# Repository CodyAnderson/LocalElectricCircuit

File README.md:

# LocalElectricCircuit

This is the repository containing the Circuit board files for the Global Electric Circuit project.

Other Global Electric Circuit project repositories can be found at:

| Repository                                                                  | Description         |
|:--------------------------------------------------------------------------- |:------------------  |
| [GlobalCircuit](https://github.com/keleuk/GlobalCircuit)                    | PIC32 code          |
| [GECaux](https://github.com/keleuk/GECaux)                                  | PIC16 code          |
| [GECutils](https://github.com/keleuk/GECutils)                              | Python scripts      |
| [LocalElectricCircuit](https://github.com/CodyAnderson/LocalElectricCircuit)| Circuit board files |

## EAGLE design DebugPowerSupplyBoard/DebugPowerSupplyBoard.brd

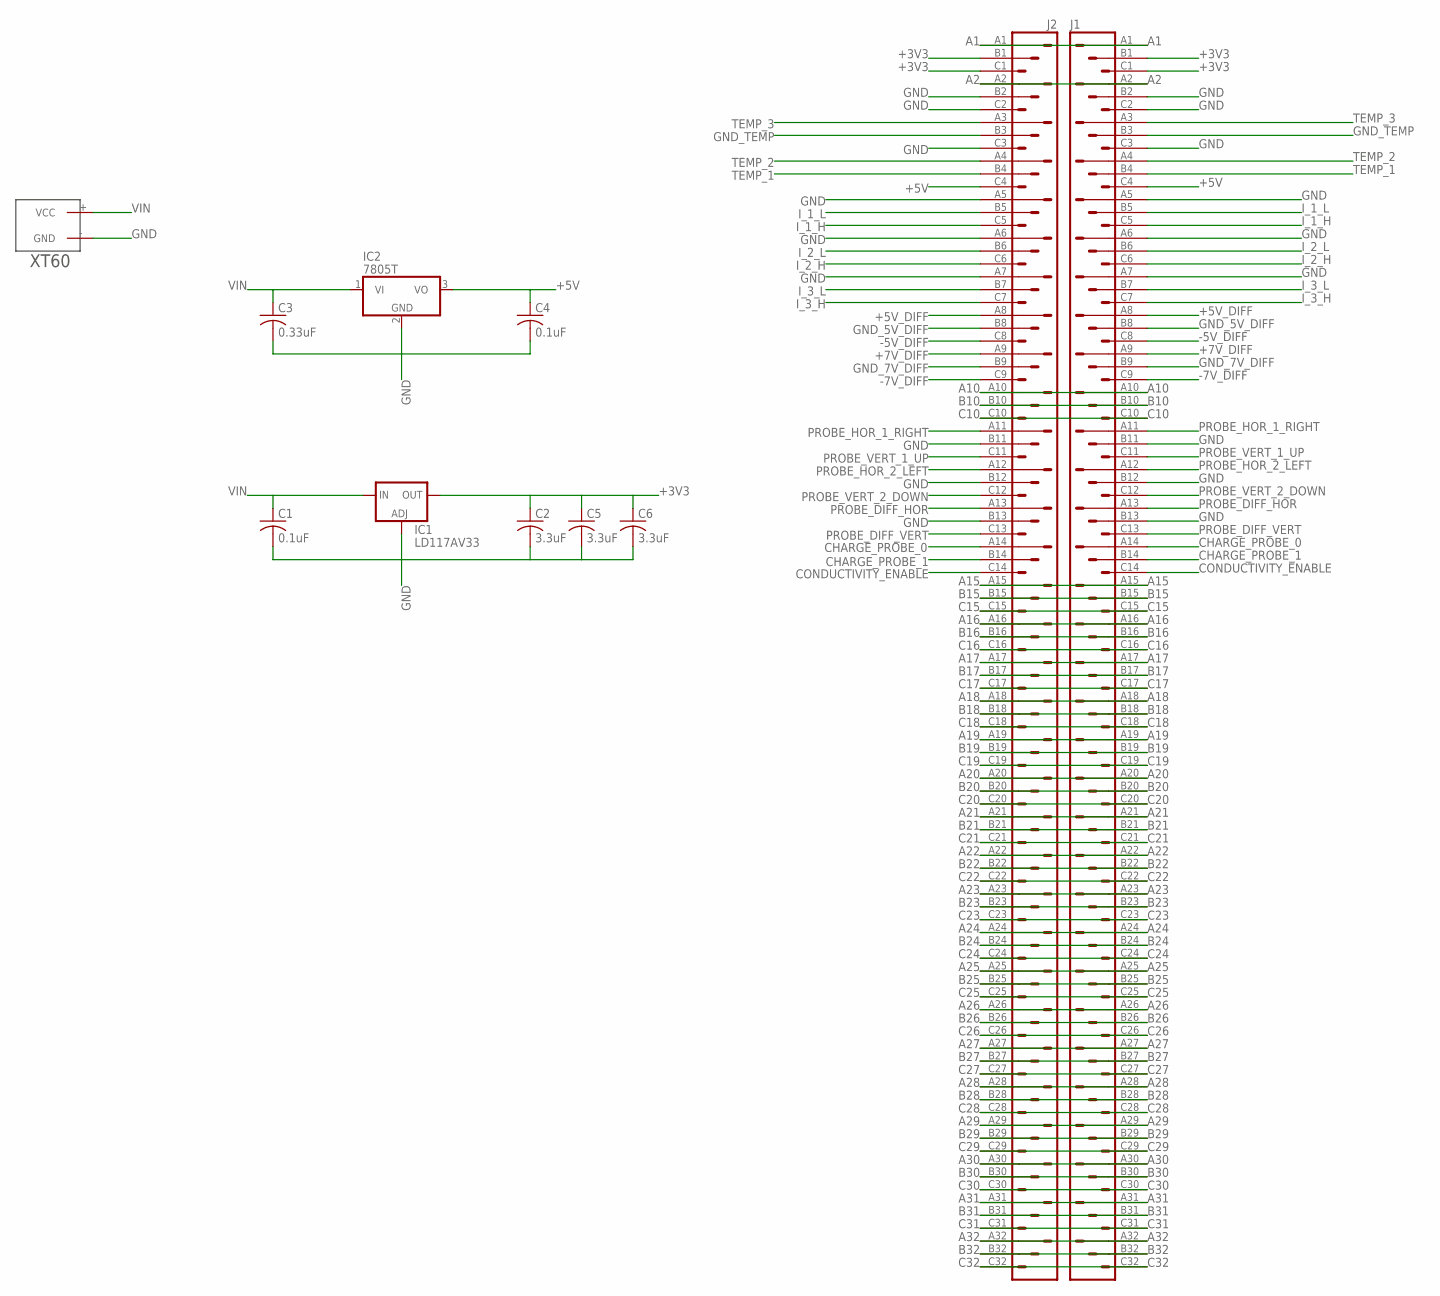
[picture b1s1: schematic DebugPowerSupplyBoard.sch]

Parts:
C1, C4: 0.1uF; C050-025X075
C2, C5, C6: 3.3uF; C050-055X075
C3: 0.33uF; C050-035X075
IC1: LD117AV33; TO220L1
IC2: 7805T; TO220H
J1, J2: VG96KB
U$6: XT60

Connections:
+3V3: C2.1, C5.1, C6.1, IC1.2 (OUT), J1.B1, J1.C1, J2.B1, J2.C1
+5V: C4.1, IC2.3 (VO), J1.C4, J2.C4
+5V_DIFF: J1.A8, J2.A8
+7V_DIFF: J1.A9, J2.A9
-5V_DIFF: J1.C8, J2.C8
-7V_DIFF: J1.C9, J2.C9
A1: J1.A1, J2.A1
A2: J1.A2, J2.A2
A10: J1.A10, J2.A10
A15: J1.A15, J2.A15
A16: J1.A16, J2.A16
A17: J1.A17, J2.A17
A18: J1.A18, J2.A18
A19: J1.A19, J2.A19
A20: J1.A20, J2.A20
A21: J1.A21, J2.A21
A22: J1.A22, J2.A22
A23: J1.A23, J2.A23
A24: J1.A24, J2.A24
A25: J1.A25, J2.A25
A26: J1.A26, J2.A26
A27: J1.A27, J2.A27
A28: J1.A28, J2.A28
A29: J1.A29, J2.A29
A30: J1.A30, J2.A30
A31: J1.A31, J2.A31
A32: J1.A32, J2.A32
B10: J1.B10, J2.B10
B15: J1.B15, J2.B15
B16: J1.B16, J2.B16
B17: J1.B17, J2.B17
B18: J1.B18, J2.B18
B19: J1.B19, J2.B19
B20: J1.B20, J2.B20
B21: J1.B21, J2.B21
B22: J1.B22, J2.B22
B23: J1.B23, J2.B23
B24: J1.B24, J2.B24
B25: J1.B25, J2.B25
B26: J1.B26, J2.B26
B27: J1.B27, J2.B27
B28: J1.B28, J2.B28
B29: J1.B29, J2.B29
B30: J1.B30, J2.B30
B31: J1.B31, J2.B31
B32: J1.B32, J2.B32
C10: J1.C10, J2.C10
C15: J1.C15, J2.C15
C16: J1.C16, J2.C16
C17: J1.C17, J2.C17
C18: J1.C18, J2.C18
C19: J1.C19, J2.C19
C20: J1.C20, J2.C20
C21: J1.C21, J2.C21
C22: J1.C22, J2.C22
C23: J1.C23, J2.C23
C24: J1.C24, J2.C24
C25: J1.C25, J2.C25
C26: J1.C26, J2.C26
C27: J1.C27, J2.C27
C28: J1.C28, J2.C28
C29: J1.C29, J2.C29
C30: J1.C30, J2.C30
C31: J1.C31, J2.C31
C32: J1.C32, J2.C32
CHARGE_PROBE_0: J1.A14, J2.A14
CHARGE_PROBE_1: J1.B14, J2.B14
CONDUCTIVITY_ENABLE: J1.C14, J2.C14
GND: C1.2, C2.2, C3.2, C4.2, C5.2, C6.2, IC1.1 (ADJ), IC2.2 (GND), J1.A5, J1.A6, J1.A7, J1.B2, J1.B11, J1.B12, J1.B13, J1.C2, J1.C3, J2.A5, J2.A6, J2.A7, J2.B2, J2.B11, J2.B12, J2.B13, J2.C2, J2.C3, U$6.- (GND)
GND_5V_DIFF: J1.B8, J2.B8
GND_7V_DIFF: J1.B9, J2.B9
GND_TEMP: J1.B3, J2.B3
I_1_H: J1.C5, J2.C5
I_1_L: J1.B5, J2.B5
I_2_H: J1.C6, J2.C6
I_2_L: J1.B6, J2.B6
I_3_H: J1.C7, J2.C7
I_3_L: J1.B7, J2.B7
PROBE_DIFF_HOR: J1.A13, J2.A13
PROBE_DIFF_VERT: J1.C13, J2.C13
PROBE_HOR_1_RIGHT: J1.A11, J2.A11
PROBE_HOR_2_LEFT: J1.A12, J2.A12
PROBE_VERT_1_UP: J1.C11, J2.C11
PROBE_VERT_2_DOWN: J1.C12, J2.C12
TEMP_1: J1.B4, J2.B4
TEMP_2: J1.A4, J2.A4
TEMP_3: J1.A3, J2.A3
VIN: C1.1, C3.1, IC1.3 (IN), IC2.1 (VI), U$6.+ (VCC)

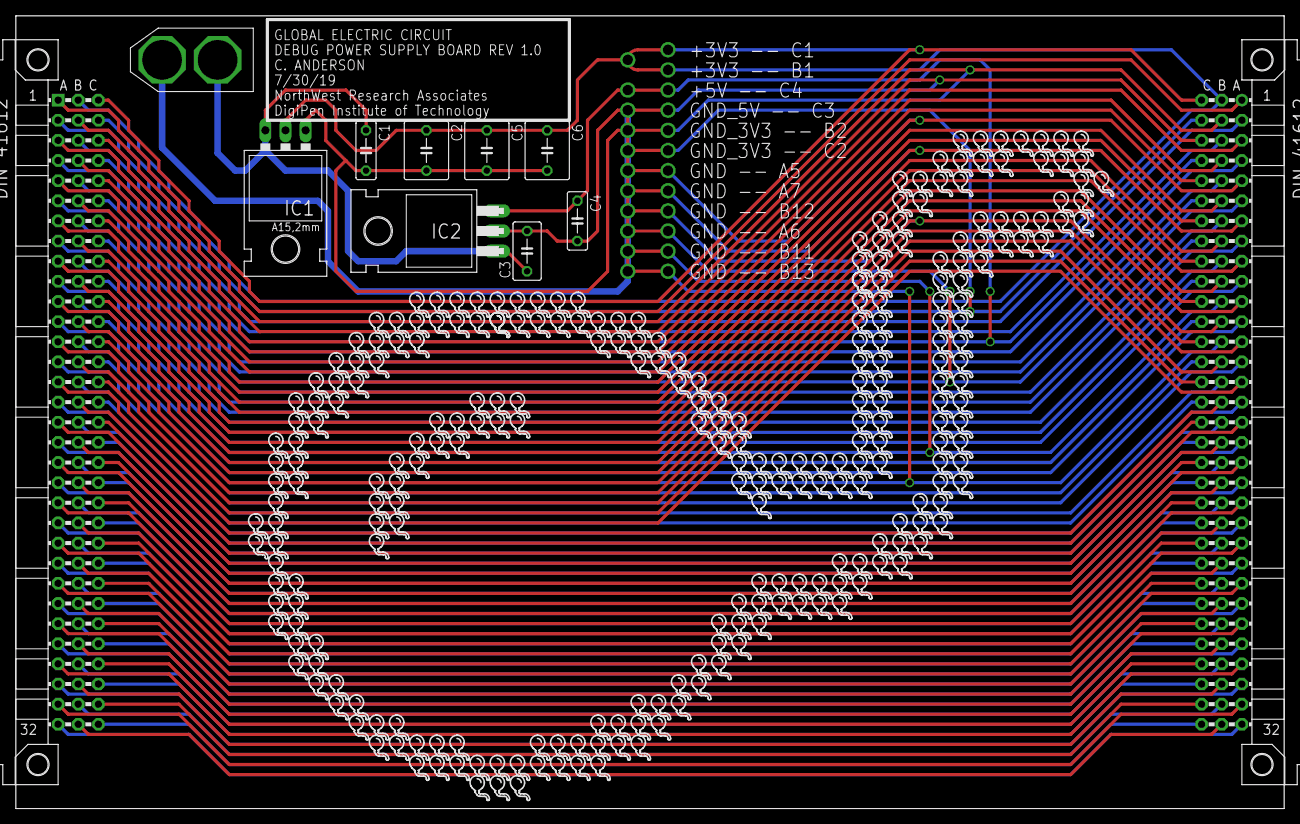
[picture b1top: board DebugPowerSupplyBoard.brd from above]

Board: 2 copper layers, 160.0 x 100.0 mm, 281 parts (0 on the bottom side), 88 nets.

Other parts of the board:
U$21, U$273, U$274, U$275, U$276, U$277, U$278, U$279, U$280, U$281, U$282, U$283, U$284, U$285, U$286, U$287, U$288, U$289, U$290, U$291, U$292, U$293, U$294, U$295, U$296, U$297, U$298, U$299, U$300, U$301, U$302, U$303, U$304, U$305, U$306, U$307, U$308, U$309, U$310, U$311, U$312, U$313, U$314, U$315, U$316, U$317, U$318, U$319, U$320, U$321, U$322, U$323, U$324, U$325, U$326, U$327, U$328, U$329, U$330, U$331, U$332, U$333, U$334, U$335, U$336, U$337, U$338, U$339, U$340, U$341, U$342, U$343, U$344, U$345, U$346, U$347, U$348, U$349, U$350, U$351, U$352, U$353, U$354, U$355, U$356, U$357, U$358, U$359, U$360, U$361, U$362, U$363, U$364, U$365, U$366, U$367, U$368, U$369, U$370, U$371, U$372, U$373, U$374, U$375, U$376, U$377, U$378, U$379, U$380, U$381, U$382, U$383, U$384, U$385, U$386, U$387, U$388, U$389, U$390, U$391, U$392, U$393, U$394, U$395, U$396, U$397, U$398, U$399, U$400, U$401, U$402, U$403, U$404, U$405, U$406, U$407, U$408, U$409, U$410, U$411, U$412, U$413, U$414, U$415, U$416, U$417, U$418, U$419, U$420, U$421, U$422, U$423, U$424, U$425, U$426, U$427, U$428, U$429, U$430, U$431, U$432, U$433, U$434, U$435, U$436, U$437, U$438, U$439, U$440, U$441, U$442, U$443, U$444, U$445, U$446, U$447, U$448, U$449, U$450, U$451, U$452, U$453, U$454, U$455, U$456, U$457, U$458, U$459, U$460, U$461, U$462, U$463, U$464, U$465, U$466, U$467, U$468, U$469, U$470, U$471, U$472, U$473, U$474, U$475, U$476, U$477, U$478, U$479, U$480, U$481, U$482, U$483, U$484, U$485, U$486, U$487, U$488, U$489, U$490, U$491, U$492, U$493, U$494, U$495, U$496, U$497, U$498, U$499, U$500, U$501, U$502, U$503, U$504, U$505, U$506, U$507, U$508, U$509, U$510, U$511, U$512, U$513, U$514, U$515, U$516, U$517, U$518, U$519, U$520, U$521, U$522, U$523, U$524, U$525, U$526, U$527, U$528, U$529, U$530, U$531, U$532, U$533, U$534, U$535, U$536, U$537, U$538, U$539, U$540, U$541: BALLOON

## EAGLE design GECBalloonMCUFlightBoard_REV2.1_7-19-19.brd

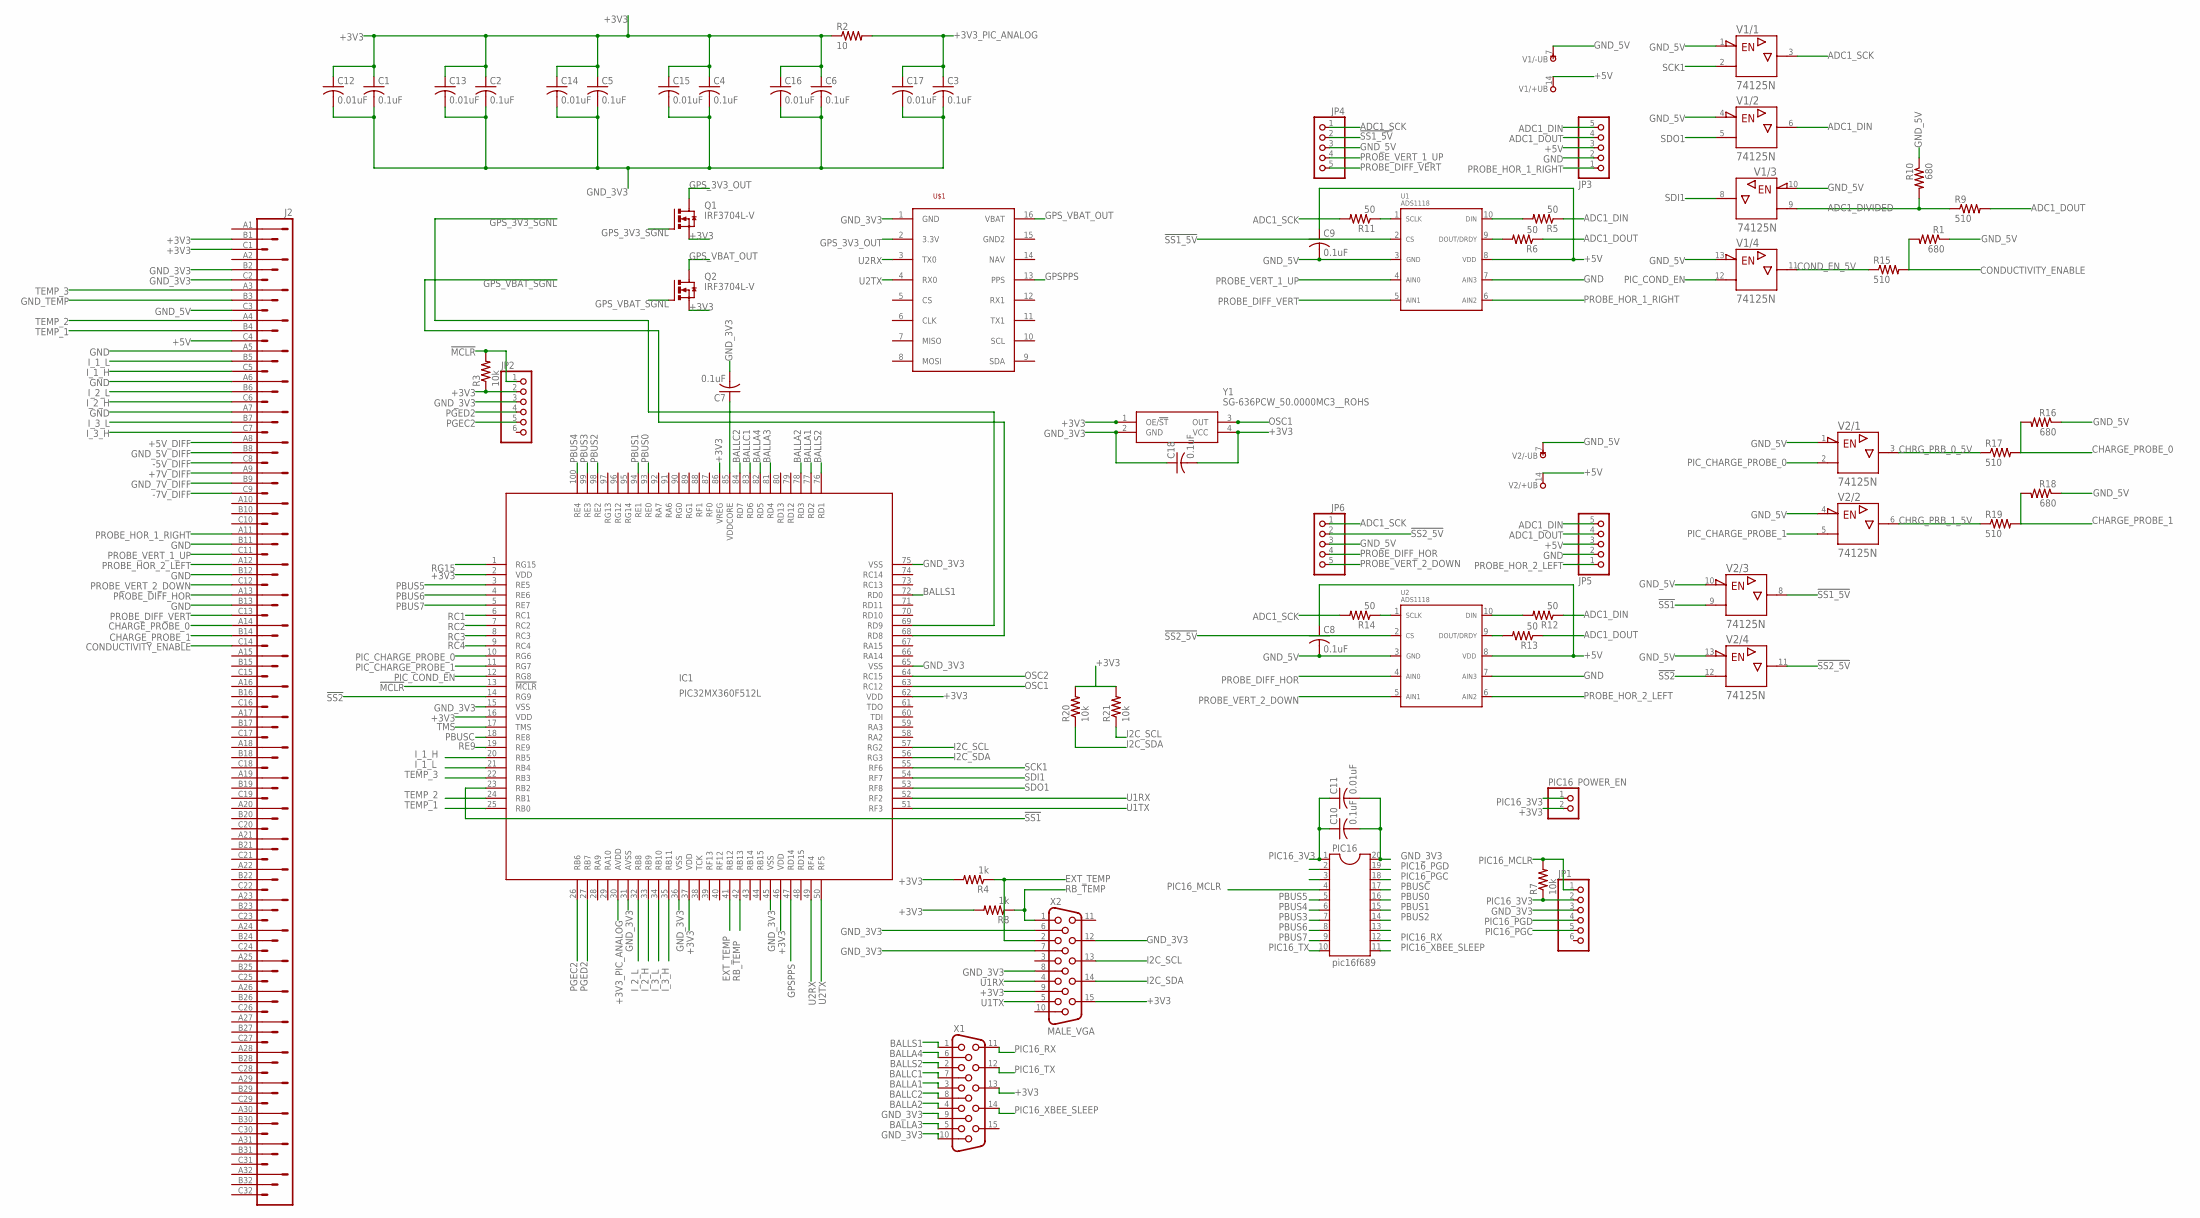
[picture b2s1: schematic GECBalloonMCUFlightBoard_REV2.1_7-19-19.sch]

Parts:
C1, C2, C3, C4, C5, C6, C7, C8, C9, C10, C18: 0.1uF; C1206
C11, C12, C13, C14, C15, C16, C17: 0.01uF; C1206
IC1: PIC32MX360F512L; TQFP100
J2: VG96KB
JP1, JP2: PINHD-1X6; 1X06
JP3, JP4, JP5, JP6: PINHD-1X5; 1X05
PIC16: pic16f689; DIL20
PIC16_POWER_EN: PINHD-1X2; 1X02
Q1, Q2: IRF3704L-V; TO262-V
R1, R10, R16, R18: 680; R1206
R2: 10; M1206
R3, R7, R20, R21: 10k; M1206
R4, R8: 1k; 0414/15
R5, R6, R11, R12, R13, R14: 50; M1206
R9, R15, R17, R19: 510; R1206
U1, U2: ADS1118; MSOP10
U$1: SPARKFUN_VENUS_GPS_BREAKOUT; SPARKFUN_BOARD
V1, V2: 74125N; DIL14
X1: HF15H; HDF15H
X2: MALE_VGA; MALE_PACKAGE
Y1: SG-636PCW_50.0000MC3__ROHS; SG-636

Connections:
!MCLR: IC1.13 (!MCLR), JP2.1, R3.2
!SS1: IC1.23 (RB2), V2.9 (A)
!SS1_5V: JP4.2, U1.2 (CS), V2.8 (Y)
!SS2: IC1.14 (RG9), V2.12 (A)
!SS2_5V: JP6.2, U2.2 (CS), V2.11 (Y)
+3V3: C1.1, C2.1, C4.1, C5.1, C6.1, C12.1, C13.1, C14.1, C15.1, C16.1, C18.2, IC1.2 (VDD), IC1.16 (VDD), IC1.37 (VDD), IC1.46 (VDD), IC1.62 (VDD), IC1.86 (VREG), J2.B1, J2.C1, JP2.2, PIC16_POWER_EN.2, Q1.3 (S), Q2.3 (S), R2.1, R3.1, R4.2, R8.2, R20.2, R21.2, X1.13, X2.9, X2.15, Y1.1 (OE/!ST), Y1.4 (VCC)
+3V3_PIC_ANALOG: C3.1, C17.1, IC1.30 (AVDD), R2.2
+5V: C8.1, C9.1, J2.C4, JP3.3, JP5.3, U1.8 (VDD), U2.8 (VDD), V1.14 (+UB), V2.14 (+UB)
+5V_DIFF: J2.A8
+7V_DIFF: J2.A9
-5V_DIFF: J2.C8
-7V_DIFF: J2.C9
ADC1_DIN: JP3.5, JP5.5, R5.1, R12.1, V1.6 (Y)
ADC1_DIVIDED: R9.1, R10.2, V1.9 (A)
ADC1_DOUT: JP3.4, JP5.4, R6.1, R9.2, R13.1
ADC1_SCK: JP4.1, JP6.1, R11.2, R14.2, V1.3 (Y)
BALLA1: IC1.77 (RD2), X1.3
BALLA2: IC1.78 (RD3), X1.4
BALLA3: IC1.81 (RD4), X1.5
BALLA4: IC1.82 (RD5), X1.6
BALLC1: IC1.83 (RD6), X1.7
BALLC2: IC1.84 (RD7), X1.8
BALLS1: IC1.72 (RD0), X1.1
BALLS2: IC1.76 (RD1), X1.2
CHARGE_PROBE_0: J2.A14, R16.2, R17.2
CHARGE_PROBE_1: J2.B14, R18.2, R19.2
CHRG_PRB_0_5V: R17.1, V2.3 (Y)
CHRG_PRB_1_5V: R19.1, V2.6 (Y)
CONDUCTIVITY_ENABLE: J2.C14, R1.2, R15.2
COND_EN_5V: R15.1, V1.11 (Y)
EXT_TEMP: IC1.41 (RB12), R4.1, X2.2
GND: J2.A5, J2.A6, J2.A7, J2.B11, J2.B12, J2.B13, JP3.2, JP5.2, U1.7 (AIN3), U2.7 (AIN3)
GND_3V3: C1.2, C2.2, C3.2, C4.2, C5.2, C6.2, C7.2, C10.2, C11.2, C12.2, C13.2, C14.2, C15.2, C16.2, C17.2, C18.1, IC1.15 (VSS), IC1.31 (AVSS), IC1.36 (VSS), IC1.45 (VSS), IC1.65 (VSS), IC1.75 (VSS), J2.B2, J2.C2, JP1.3, JP2.3, PIC16.20, U$1.1 (GND), X1.9, X1.10, X2.6, X2.7, X2.8, X2.12, Y1.2 (GND)
GND_5V: C8.2, C9.2, J2.C3, JP4.3, JP6.3, R1.1, R10.1, R16.1, R18.1, U1.3 (GND), U2.3 (GND), V1.1 (!G), V1.4 (!G), V1.7 (-UB), V1.10 (!G), V1.13 (!G), V2.1 (!G), V2.4 (!G), V2.7 (-UB), V2.10 (!G), V2.13 (!G)
GND_5V_DIFF: J2.B8
GND_7V_DIFF: J2.B9
GND_TEMP: J2.B3
GPSPPS: IC1.47 (RD14), U$1.13 (PPS)
GPS_3V3_OUT: Q1.2 (D), U$1.2 (3.3V)
GPS_3V3_SGNL: IC1.69 (RD9), Q1.1 (G)
GPS_VBAT_OUT: Q2.2 (D), U$1.16 (VBAT)
GPS_VBAT_SGNL: IC1.68 (RD8), Q2.1 (G)
I2C_SCL: IC1.57 (RG2), R21.1, X2.13
I2C_SDA: IC1.56 (RG3), R20.1, X2.14
I_1_H: IC1.20 (RB5), J2.C5
I_1_L: IC1.21 (RB4), J2.B5
I_2_H: IC1.33 (RB9), J2.C6
I_2_L: IC1.32 (RB8), J2.B6
I_3_H: IC1.35 (RB11), J2.C7
I_3_L: IC1.34 (RB10), J2.B7
unnamed: R5.2, U1.10 (DIN)
unnamed: R6.2, U1.9 (DOUT/DRDY)
unnamed: R11.1, U1.1 (SCLK)
unnamed: R12.2, U2.10 (DIN)
unnamed: R13.2, U2.9 (DOUT/DRDY)
unnamed: R14.1, U2.1 (SCLK)
OSC1: IC1.63 (RC12), Y1.3 (OUT)
OSC2: IC1.64 (RC15)
PBUS0: IC1.93 (RE0), PIC16.16
PBUS1: IC1.94 (RE1), PIC16.15
PBUS2: IC1.98 (RE2), PIC16.14
PBUS3: IC1.99 (RE3), PIC16.7
PBUS4: IC1.100 (RE4), PIC16.6
PBUS5: IC1.3 (RE5), PIC16.5
PBUS6: IC1.4 (RE6), PIC16.8
PBUS7: IC1.5 (RE7), PIC16.9
PBUSC: IC1.18 (RE8), PIC16.17
PGEC2: IC1.26 (RB6), JP2.5
PGED2: IC1.27 (RB7), JP2.4
PIC16_3V3: C10.1, C11.1, JP1.2, PIC16.1, PIC16_POWER_EN.1, R7.1
PIC16_MCLR: JP1.1, PIC16.4, R7.2
PIC16_PGC: JP1.5, PIC16.18
PIC16_PGD: JP1.4, PIC16.19
PIC16_RX: PIC16.12, X1.11
PIC16_TX: PIC16.10, X1.12
PIC16_XBEE_SLEEP: PIC16.11, X1.14
PIC_CHARGE_PROBE_0: IC1.10 (RG6), V2.2 (A)
PIC_CHARGE_PROBE_1: IC1.11 (RG7), V2.5 (A)
PIC_COND_EN: IC1.12 (RG8), V1.12 (A)
PROBE_DIFF_HOR: J2.A13, JP6.4, U2.4 (AIN0)
PROBE_DIFF_VERT: J2.C13, JP4.5, U1.5 (AIN1)
PROBE_HOR_1_RIGHT: J2.A11, JP3.1, U1.6 (AIN2)
PROBE_HOR_2_LEFT: J2.A12, JP5.1, U2.6 (AIN2)
PROBE_VERT_1_UP: J2.C11, JP4.4, U1.4 (AIN0)
PROBE_VERT_2_DOWN: J2.C12, JP6.5, U2.5 (AIN1)
RB_TEMP: IC1.42 (RB13), R8.1, X2.1
RC1: IC1.6 (RC1)
RC2: IC1.7 (RC2)
RC3: IC1.8 (RC3)
RC4: IC1.9 (RC4)
RE9: IC1.19 (RE9)
RG15: IC1.1 (RG15)
SCK1: IC1.55 (RF6), V1.2 (A)
SDI1: IC1.54 (RF7), V1.8 (Y)
SDO1: IC1.53 (RF8), V1.5 (A)
TEMP_1: IC1.25 (RB0), J2.B4
TEMP_2: IC1.24 (RB1), J2.A4
TEMP_3: IC1.22 (RB3), J2.A3
TMS: IC1.17 (TMS)
U1RX: IC1.52 (RF2), X2.4
U1TX: IC1.51 (RF3), X2.5
U2RX: IC1.49 (RF4), U$1.3 (TX0)
U2TX: IC1.50 (RF5), U$1.4 (RX0)
VCAP/VCORE: C7.1, IC1.85 (VDDCORE)

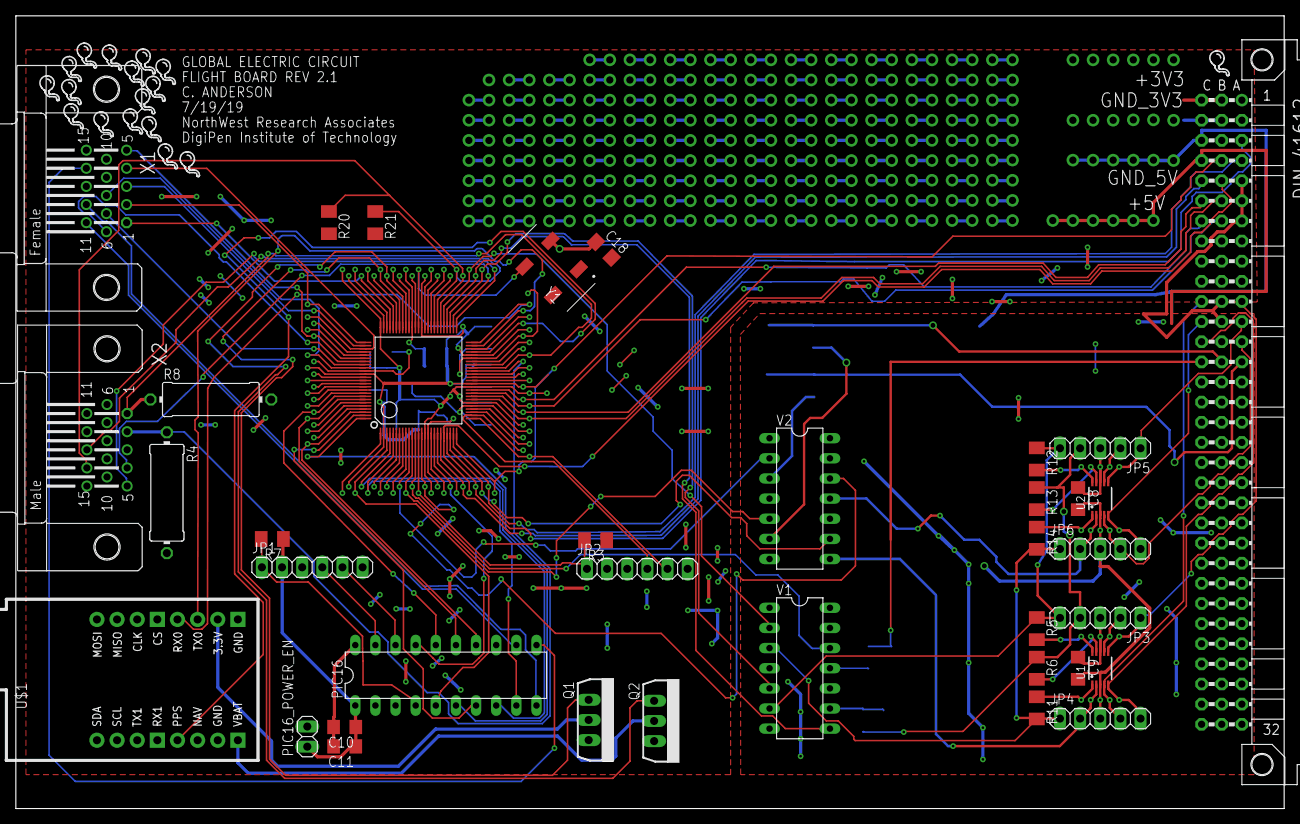
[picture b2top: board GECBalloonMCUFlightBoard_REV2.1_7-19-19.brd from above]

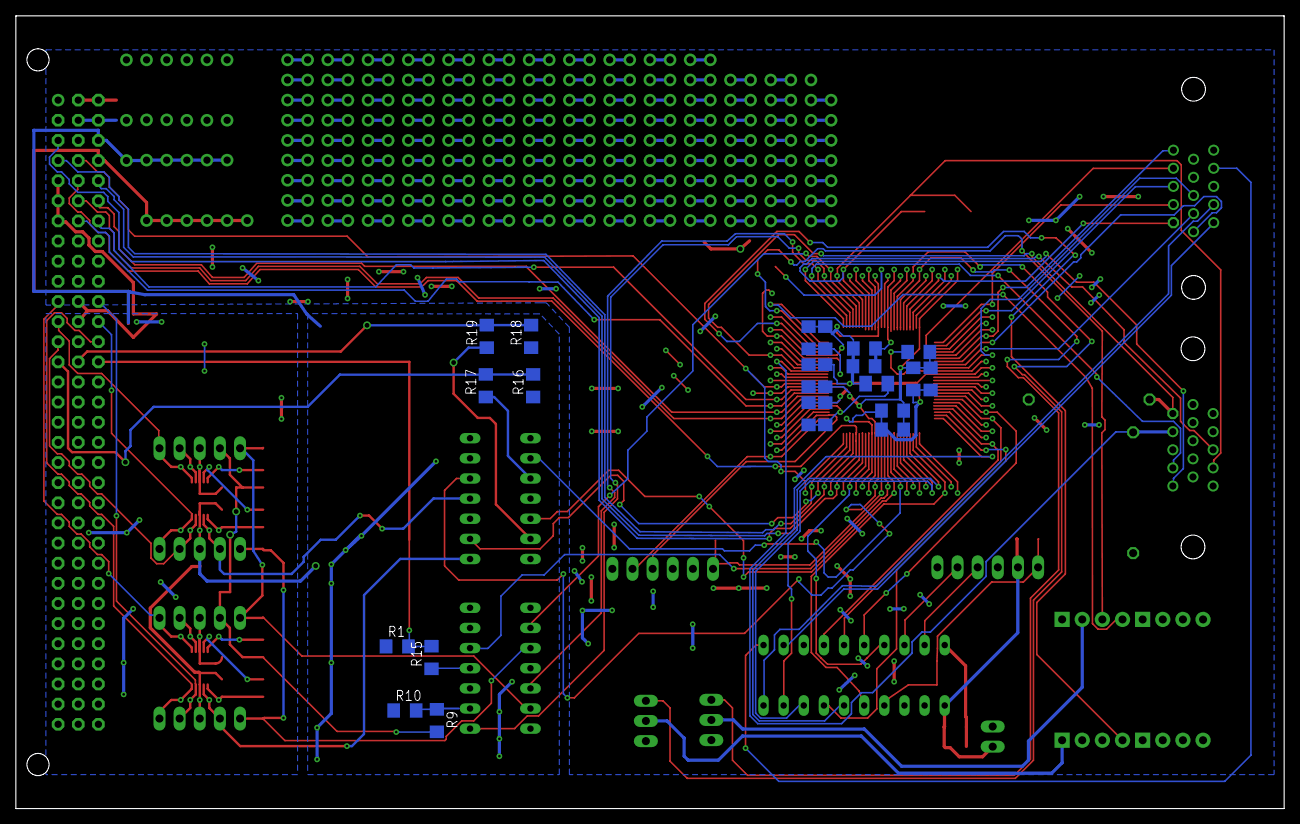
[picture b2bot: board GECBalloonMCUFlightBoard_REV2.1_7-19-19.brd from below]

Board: 2 copper layers, 160.0 x 100.0 mm, 76 parts (22 on the bottom side), 89 nets.

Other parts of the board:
U$2, U$3, U$4, U$5, U$6, U$7, U$8, U$9, U$10, U$11, U$12, U$14, U$15, U$16, U$17, U$19, U$21: BALLOON

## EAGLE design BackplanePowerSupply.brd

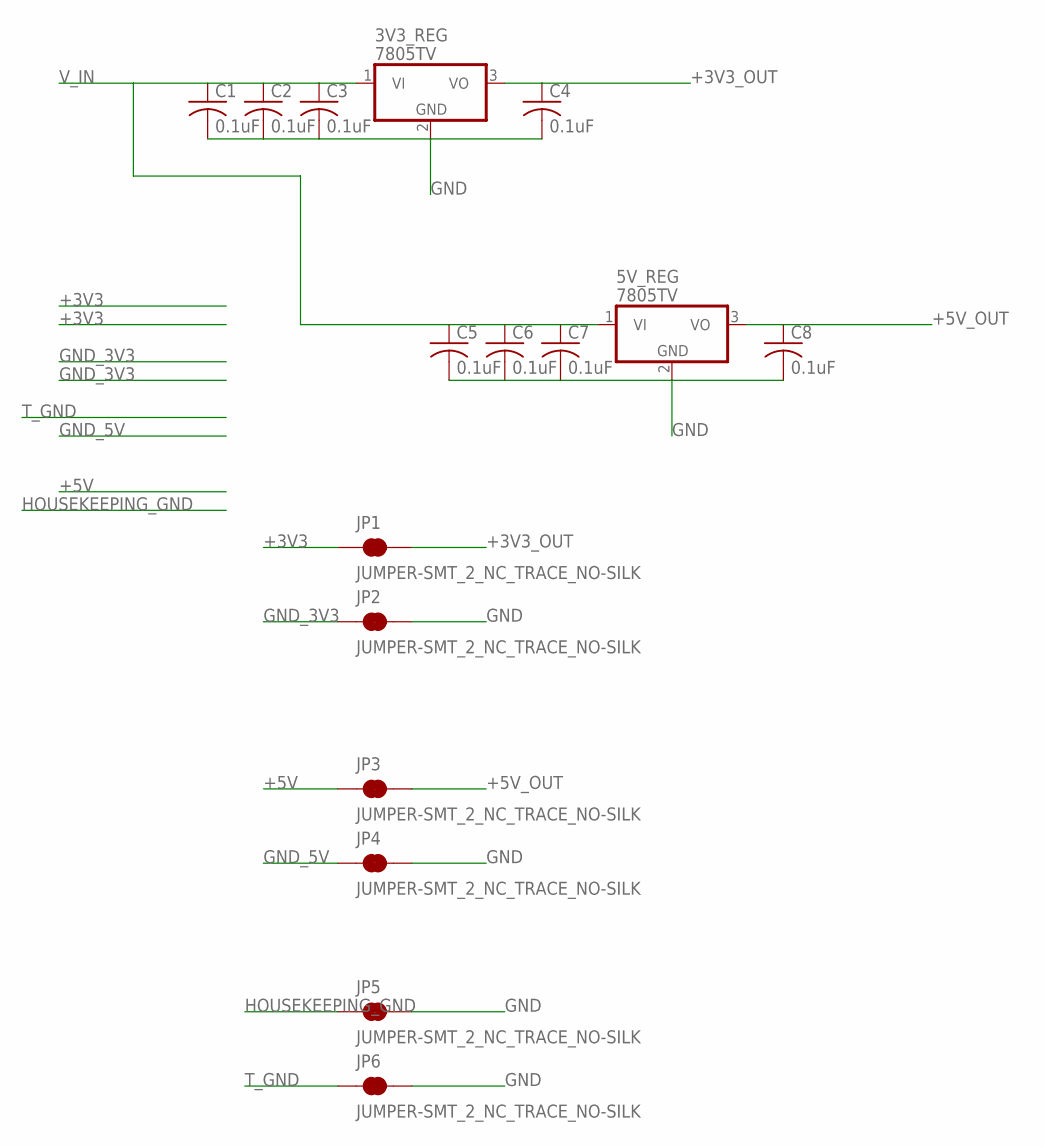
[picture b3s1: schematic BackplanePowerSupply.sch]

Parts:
3V3_REG, 5V_REG: 7805TV; TO220V
C1, C2, C3, C4, C5, C6, C7, C8: 0.1uF; C050-025X075
JP1, JP2, JP3, JP4, JP5, JP6: JUMPER-SMT_2_NC_TRACE_NO-SILK; SMT-JUMPER_2_NC_TRACE_NO-SILK

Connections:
+3V3: JP1.1
+3V3_OUT: 3V3_REG.3 (VO), C4.1, JP1.2
+5V: JP3.1
+5V_OUT: 5V_REG.3 (VO), C8.1, JP3.2
GND: 3V3_REG.2 (GND), 5V_REG.2 (GND), C1.2, C2.2, C3.2, C4.2, C5.2, C6.2, C7.2, C8.2, JP2.2, JP4.2, JP5.2, JP6.2
GND_3V3: JP2.1
GND_5V: JP4.1
HOUSEKEEPING_GND: JP5.1
T_GND: JP6.1
V_IN: 3V3_REG.1 (VI), 5V_REG.1 (VI), C1.1, C2.1, C3.1, C5.1, C6.1, C7.1

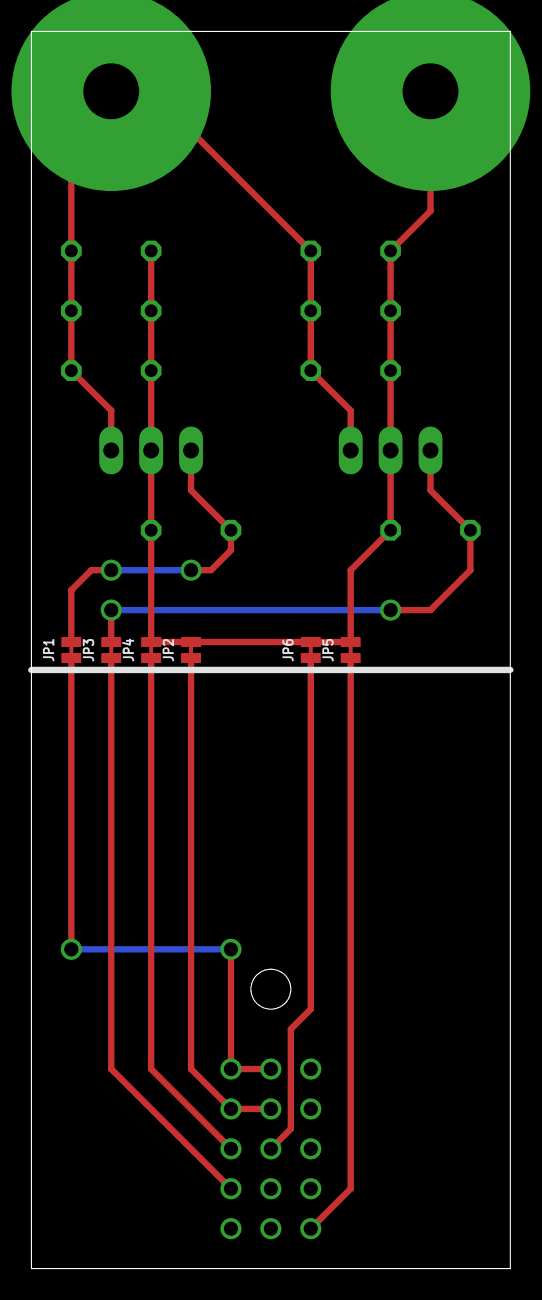
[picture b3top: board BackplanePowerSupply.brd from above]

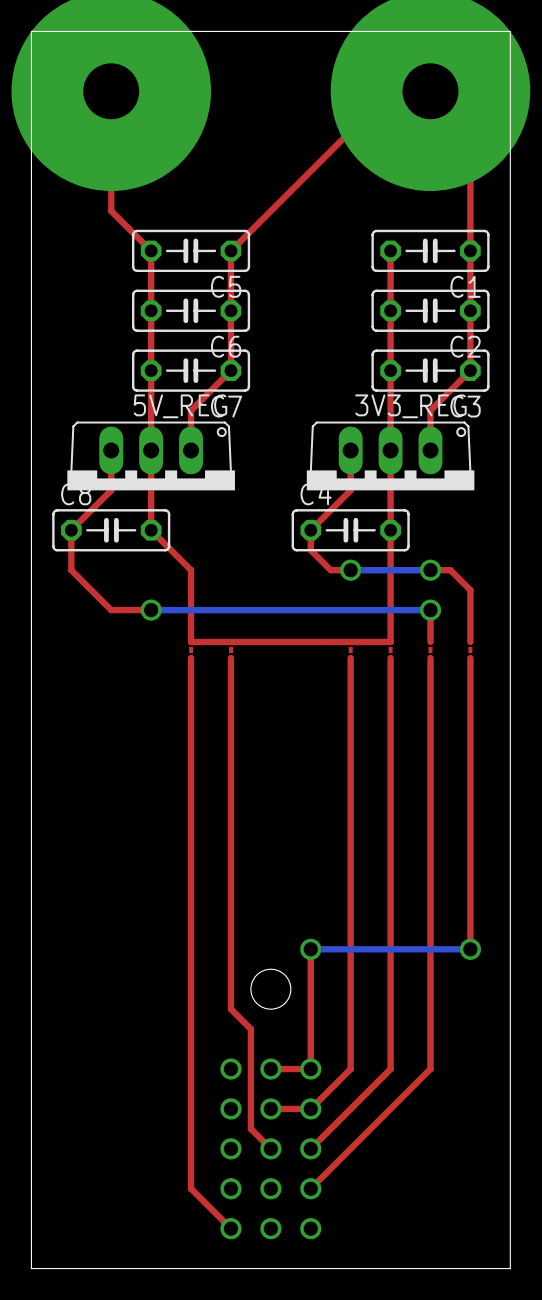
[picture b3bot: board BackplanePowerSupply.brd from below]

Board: 2 copper layers, 30.5 x 78.7 mm, 16 parts (10 on the bottom side), 4 nets.

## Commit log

2018-08-08 Here it is, worlsd
2018-08-08 Added PIC16
2018-08-08 Connected PIC16 to DB connector
2018-08-08 Connected PIC32 analog pins
2018-08-08 Ballast pins added
2018-08-08 Added conductivity pins
2018-08-08 Added I2C labels
2018-08-08 Well, I hope this got it all in there 😭
2018-08-08 aware of dog pleas pet dog
2018-08-08 Oh boy o"bertor
2018-08-08 Getting there
2018-08-08 Unlocked files
2018-08-08 Started early layout
2018-08-08 Transistor circuit updated to be active high and to save power.
2018-08-08 ADDED ADC RESISTORS DONT KNOW HOW TO USE GITHUB IM SORRY IN ADVANCE
2018-08-08 CHANGED NAMES OF THE NETS LOTS OF TORNADOS COMING SOON NOW WE CAN PROGARM
2018-08-09 I ADDED A LIST ITS A LIST OF THINGS WE MISSED WE NEED THEM BE FIXED
2018-08-09 THIS HERE PIC32 COULD JUST NOT LEARN ANYTHING NEW UNTIL NETS RENAMED WERE TWO
2018-08-09 Mild layout changes
2018-08-09 GND planes and some layout bizz
2018-08-09 It's a healthy baby board!
2018-08-09 ✋✋✋✋✋hol' up hol' up ✋✋ looks 👀 like we got a master 🎓 memer 🐸🐸🐸 over here 👈👈👈
2018-08-09 According to all known laws of aviation, there is no way a 🅱 should be able to fly.
2018-08-09 Robot router
2018-08-09 EEEAAAAGGGLGLLLLEEEEE
2018-08-09 Woo-hoo
2018-08-09 gO gO POWER RANGERS
2018-08-09 Fixed a whole ton of issues from DRC Figured out there were vias stacked on eachother which caused 'Drill Distance' error Figured out that the radius around vias was set smaller than the general gap 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
2018-08-09 Wired some air and stopped some t's an 🅱's
2018-08-09 LETTERS ON SILK SCREEN COVERING PADS ON FEILDS OF GREEN THREE BOYZ MISS MEETING
2018-08-09 Added board name and credits and whatnot
2018-08-09 So far I've only ripped up a trace to have something to commit for the new branch
2018-08-09 Yeet
2018-08-09 There once was a jumper for PIC The planes it connected were thicc But the ends were the same In both function and name So I have to delete it, and quick
2018-08-09 Take 2
2018-08-09 There once was a man who, for sport Adjusted the programming port. It made new airwires, And caused a great fire, In the end, his employment was short.
2018-08-10 Fan out step numero uno
2018-08-10 I'm a FAN of this pinout 😁 Am I right, laides 😉
2018-08-10 Auto router did a goody
2018-08-10 Power plane progress
2018-08-10 Tapping out
2018-08-10 Docs
2018-08-10 Minor DRC fixes.
2018-08-10 Updated PDF's
2018-08-13 Schematic PDF
2018-08-13 Added Male VGA part
2018-08-13 male VGA connector has been auto-routed
2018-08-15 Fixed planes, resistor collision
2018-08-21 Update silk screen with REv 1.0 and date Added fan out for all PIC pins Began on fan out for ADC pins ETC.
2018-08-21 Did a whole ton of stuff. Added the level-shifting hardware Added fan out for ADC's Worked on clearing some DRC errors ETC
2018-08-22 Pre auto-route
2018-08-22 Actually pre auto routing
2018-08-22 Ugh🎈
2018-08-22 VIAS STOOD ALONE FIELDS OF CIRCLES, MILLIMETERS BETWEEN COPY PASTA RIPPY UPPY DONE
2018-08-22 Fixing problems
2018-08-22 Renamed the files to contain the Revision number in them. Also deleted a bunch of useless backup files and also renamed the rendered .pdfs to have more descriptive names.
2018-08-23 Updated .pdfs
2018-08-23 THIS IS THE VERSION OF THE BOARD SENT TO BE MADE
2018-08-23 Renamed files for a more professional look
2018-09-04 Connected GPS PPS signal
2018-10-12 First attempt at making a direct-to-board mount for the wiring harness type of connector.
2018-10-12 Widened the vias for the test board
2018-10-12 Two VGA's at the same time
2018-10-12 VGA pins ready to be routed
2018-10-27 Updated VGA hack board
2018-10-27 Updated VGA hcak board more Should now have spots for I2C and UART connections
2018-11-19 Various changes to the board. With this, the testing setup has been functional for quite a while...
2018-11-19 COnnected GPSPPS pin and Incremented revision number
2018-11-24 Swapped out oscillator for external crystal clock and connected GND and 3V3 planes better.
2018-11-24 Added capacitor for external crystal
2018-11-24 Added Eagle lock file to gitignore
2018-11-24 Added all board backup files ('.b#1', '.b#2', etc.) and schematic backup files ('.s#1', '.s#2', etc.) to gitignore up to a depth of 9
2019-05-03 Added gitignore entry for backup schematic files and backup board files of the format *.b## and *.s##, respectively
2019-05-03 Added PIC16_XBEE_SLEEP pin to the VGA connector X1 on PIN14
2019-05-04 Added GPS power mosfet and GPS standby mosfet.
2019-05-06 So far, manage to rip up old traces without totally losing the PIC32's fan out
2019-05-06 Part way done
2019-05-06 Routed a lot of signals, fixed a lot of errors and nearly lost my mind. Everything on my checklist is complete now, though.
2019-05-06 Renamed the board file with an appropriately dated name and generated some pdfs for Jeremy to look at.
2019-05-16 Added chart of what values the resistors + capacitors on the bottom of the board need
2019-06-04 Added breakout boards for magnetometer, altimeter, and UART
2019-06-05 Fixed Altimeter PS pin connection on breakout board (was connected to GND, now connected to VCC)
2019-06-05 Made breakout board more aesthetic
2019-06-06 Made both breakout boards REALLY aesthetic, also they self document now
2019-06-07 Adjusted postion of input labels on breakout boards so they're not partially covered by screw terminals
2019-07-18 Skidaddle! Skidoodle! Your board is now a noodle!
2019-07-19 Added another ground pin to the DB15 connector and fixed the resistor layout to work with the temp sensors
2019-07-19 Added onboard I2C pullup resistors
2019-07-19 Renamed board files to represent the current date and revision. Also archived the version of the board sent out in the OldBoardRevisions folder
2019-07-19 Archived the board files and generated .pdfs This time I did so proactively 👍
2019-07-19 Hey, why not include this .zip? 🤔 It actually works as a super reliable archive of the versions of the files I sent to Kit and Jeremy.
2019-07-22 Deleted the .lck files eagle generates to 'lock' the board files
2019-07-23 Got the circuit of the regulator board down
2019-07-24 Progress was made
2019-07-26 Changed the capacitors used to be ones which are readily avaliable from DigiKey
2019-07-26 Routed the upper half of the traces for the board
2019-07-27 Moved all the traces near the bottom of the board
2019-07-27 Added the XT60 connector. Almost done with this cursed board
2019-07-27 All the grounds are 'connected'. Just about to rename them to finalize it
2019-07-27 All the grounds have the same name now, so Eagle knows to connect them.
2019-07-27 Labeled all the GND etc. pins and applied the decal
2019-07-27 Alright, got it perfect, including adding a box around the board label ❤
2019-07-30 Updated I2C board
2019-07-30 Added words to I2C board
2019-07-30 Finished the board
2019-07-30 Bloon
2020-11-22 Update chordtoll's username in repo links

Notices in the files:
parts and their libraries:
SparkFun-Jumpers: Licensing: Creative Commons ShareAlike 4.0 International - https://creativecommons.org/licenses/by-sa/4.0
